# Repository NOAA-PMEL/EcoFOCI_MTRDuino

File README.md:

# EcoFOCI_MTRDuino

Arduino Version of PMEL's MTR (Miniature Temperature Recorder)

################

Legal Disclaimer

This repository is a software product and is not official communication of the National Oceanic and Atmospheric Administration (NOAA), or the United States Department of Commerce (DOC). All NOAA GitHub project code is provided on an 'as is' basis and the user assumes responsibility for its use. Any claims against the DOC or DOC bureaus stemming from the use of this GitHub project will be governed by all applicable Federal law. Any reference to specific commercial products, processes, or services by service mark, trademark, manufacturer, or otherwise, does not constitute or imply their endorsement, recommendation, or favoring by the DOC. The DOC seal and logo, or the seal and logo of a DOC bureau, shall not be used in any manner to imply endorsement of any commercial product or activity by the DOC or the United States Government.

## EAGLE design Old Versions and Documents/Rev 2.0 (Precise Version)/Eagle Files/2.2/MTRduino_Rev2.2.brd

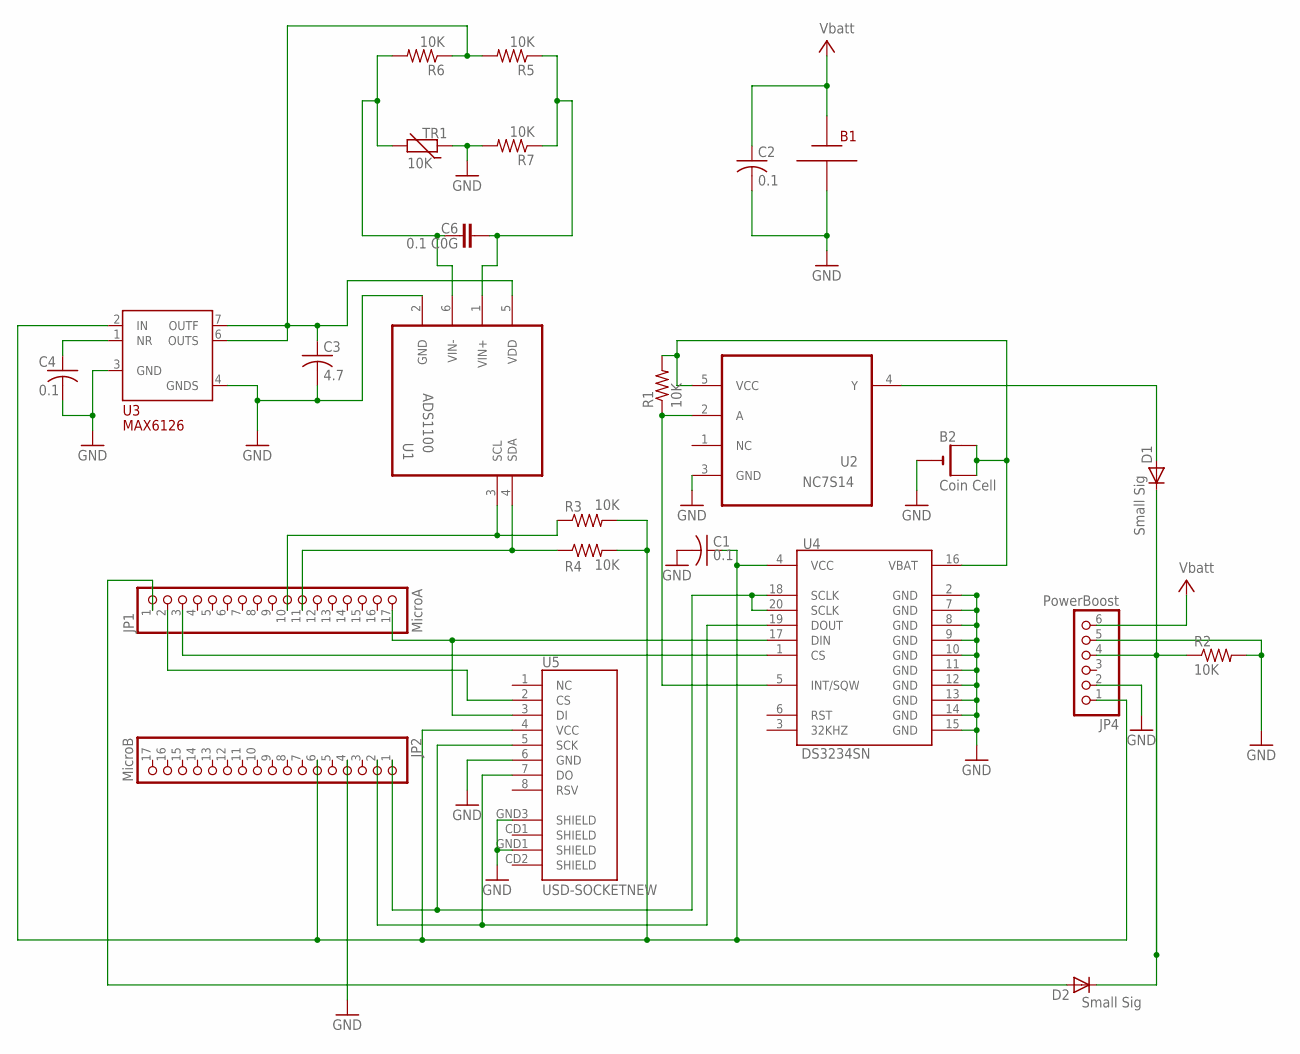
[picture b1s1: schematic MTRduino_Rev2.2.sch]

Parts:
B1: 2x AA BATT; BATT_AA2
B2: Coin Cell; CR1220-SMD
C1, C2, C4: 0.1; C0603
C3: 4.7; C0603
C6: 0.1 C0G; C0603
D1, D2: Small Sig; SOD-323F
JP1: MicroA; 1X17
JP2: MicroB; 1X17
JP4: PowerBoost; 1X06
R1, R2, R3, R4, R5, R6, R7: 10K; R0603
TR1: 10K; R-5
U1: ADS1100; SOT95P280X145-6N
U2: NC7S14; SOT95P280X145-5N
U3: MAX6126; SOIC127P600X175-8N
U4: DS3234SN; DS3234
U5: USD-SOCKETNEW; MICRO-SD-SOCKET-PP

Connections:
GND: B1.-, B2.-, C1.2, C2.2, C3.2, C4.2, JP2.4, JP4.2, JP4.5, R2.2, R7.2, TR1.1, U1.2 (GND), U2.3 (GND), U3.3 (GND), U3.4 (GNDS), U4.2 (GND), U4.7 (GND), U4.8 (GND), U4.9 (GND), U4.10 (GND), U4.11 (GND), U4.12 (GND), U4.13 (GND), U4.14 (GND), U4.15 (GND), U5.6 (GND), U5.GND1 (SHIELD), U5.GND3 (SHIELD)
unnamed: D1.A, U2.4 (Y)
unnamed: C6.1, R6.2, TR1.2, U1.6 (VIN-)
unnamed: JP1.3, U4.1 (CS)
unnamed: C4.1, U3.1 (NR)
unnamed: C6.2, R5.1, R7.1, U1.1 (VIN+)
unnamed: B2.+$1 (+), B2.+$2 (+1), R1.2, U2.5 (VCC), U4.16 (VBAT)
unnamed: JP1.17, U4.17 (DIN), U5.3 (DI)
unnamed: JP1.10, R3.1, U1.3 (SCL)
unnamed: JP1.11, R4.1, U1.4 (SDA)
unnamed: C3.1, R5.2, R6.1, U1.5 (VDD), U3.6 (OUTS), U3.7 (OUTF)
unnamed: R1.1, U2.2 (A), U4.5 (INT/SQW)
unnamed: JP2.2, U4.19 (DOUT), U5.7 (DO)
unnamed: D2.A, JP1.1
unnamed: D1.C, D2.C, JP4.4, R2.1
unnamed: JP2.1, U4.18 (SCLK), U4.20 (SCLK), U5.5 (SCK)
unnamed: C1.1, JP2.6, JP4.1, R3.2, R4.2, U3.2 (IN), U4.4 (VCC), U5.4 (VCC)
unnamed: JP1.2, U5.2 (CS)
V+: B1.+, C2.1, JP4.6

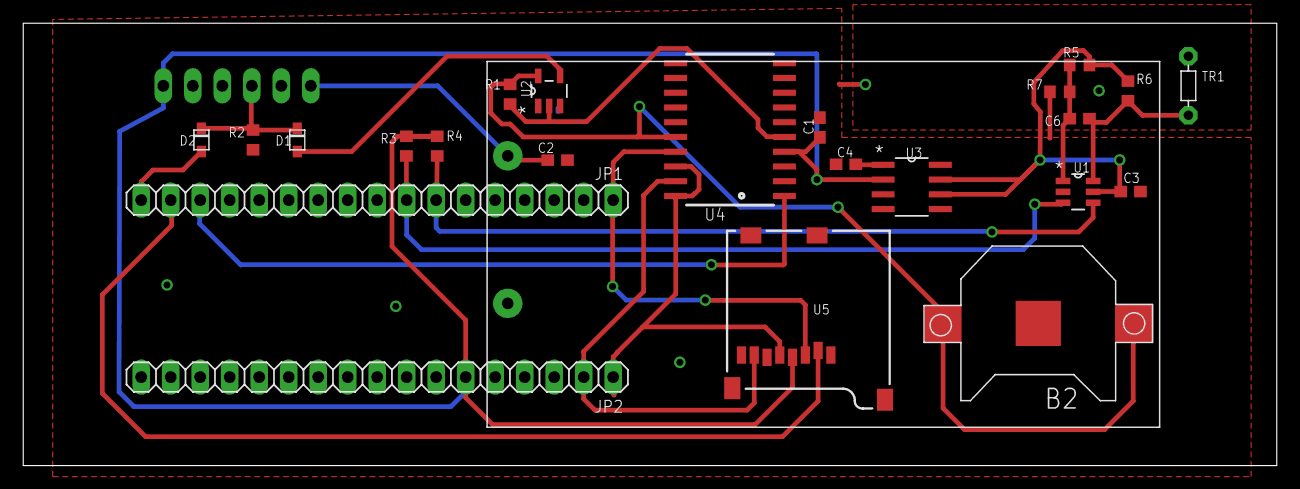
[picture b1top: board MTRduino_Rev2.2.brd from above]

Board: 2 copper layers, 107.9 x 38.1 mm, 25 parts (1 on the bottom side), 19 nets.

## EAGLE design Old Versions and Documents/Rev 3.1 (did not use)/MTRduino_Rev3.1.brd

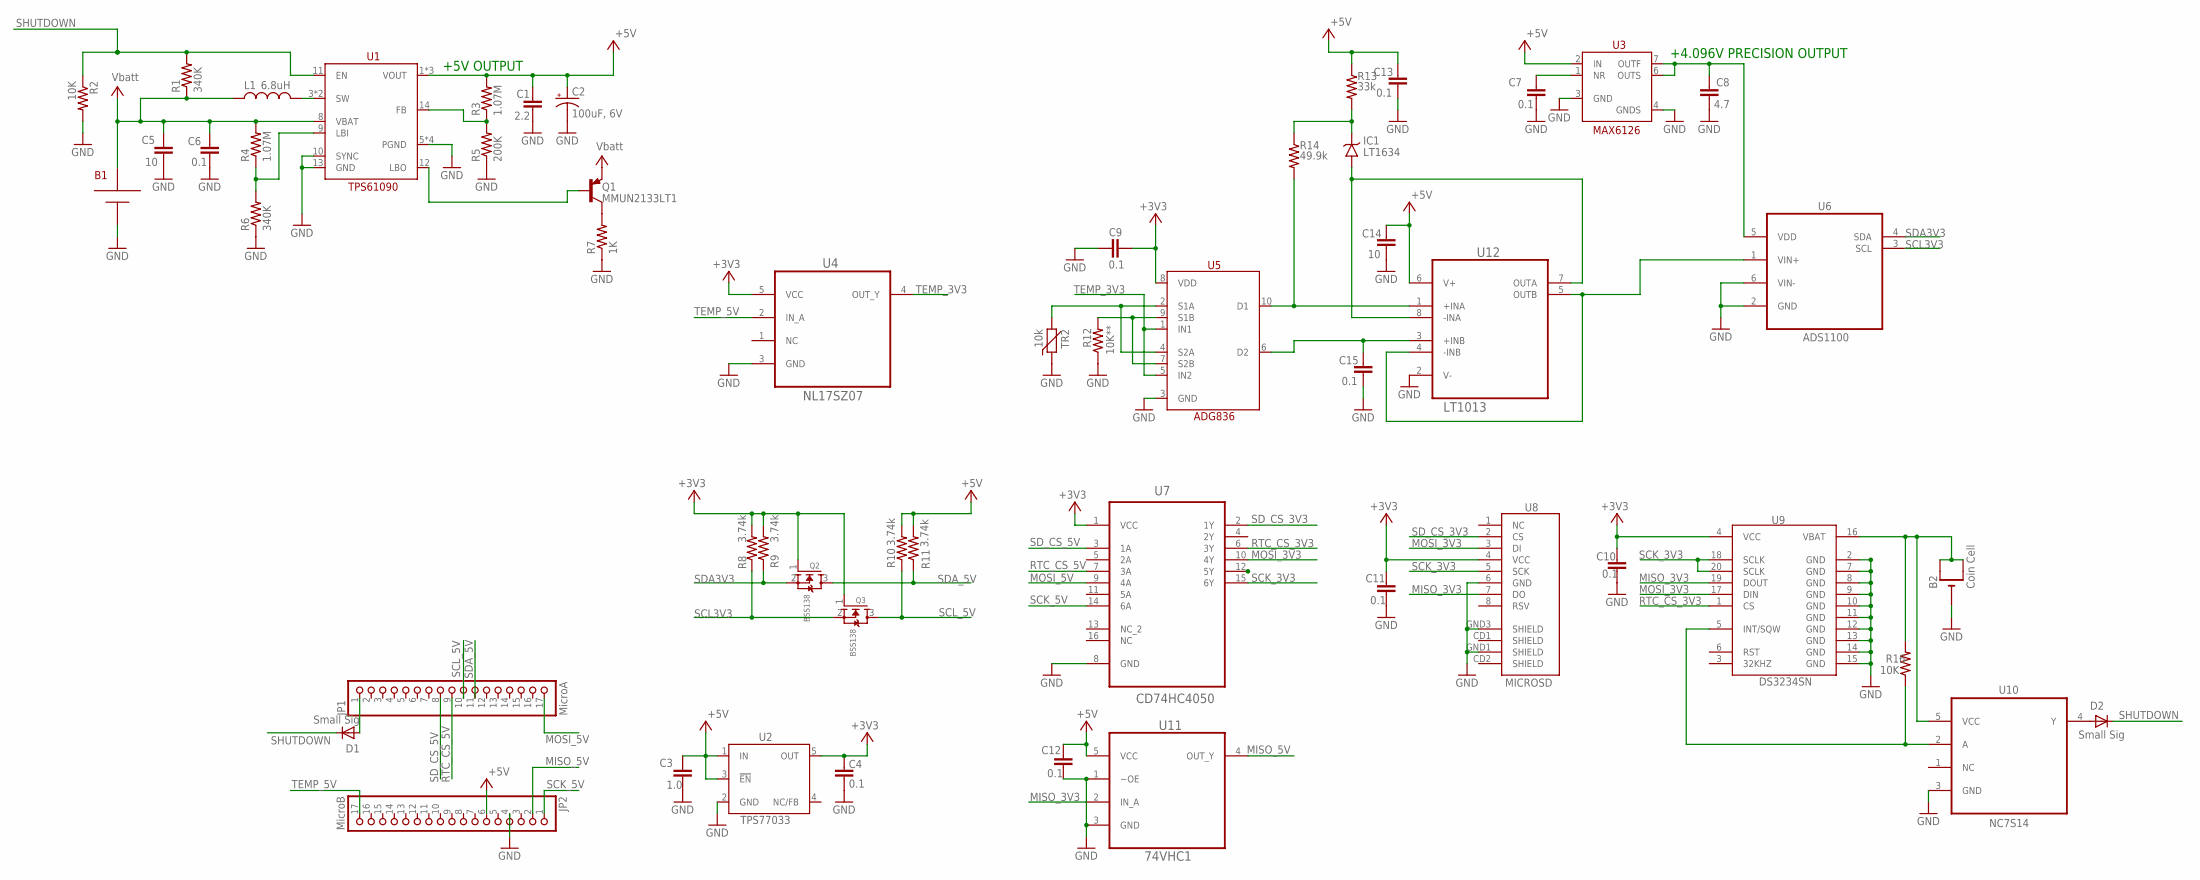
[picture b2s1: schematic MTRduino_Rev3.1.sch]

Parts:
B1: 2x AA BATT; BATT_AA2
B2: Coin Cell; CR1220-SMD
C1: 2.2; C0603
C2: 100uF, 6V; A/3216-18R
C3: 1.0; C0603
C4, C6, C7, C9, C10, C11, C12, C13, C15: 0.1; C0603
C5, C14: 10; C0603
C8: 4.7; C0603
D1, D2: Small Sig; SOD-323F
IC1: LT1634; S8
JP1: MicroA; 1X17
JP2: MicroB; 1X17
L1: 6.8uH; L2012C
Q1: MMUN2133LT1; SC59-BEC
Q2, Q3: BSS138; SOT23
R1, R6: 340K; R0603
R2, R16: 10K; R0603
R3, R4: 1.07M; R0603
R5: 200K; R0603
R7: 1K; R0603
R8, R9, R10, R11: 3.74k; R0603
R12: 10K**; R1206
R13: 33k; R0603
R14: 49.9k; R0603
TR2: 10k; R-5
U1: TPS61090; QFN16-4X4
U2: TPS77033; SOT23-DBV
U3: MAX6126; SOIC127P600X175-8N
U4: NL17SZ07; SOT65P210X110-5N
U5: ADG836; MSOP10
U6: ADS1100; SOT95P280X145-6N
U7: CD74HC4050; SOIC127P600X175-16N
U8: MICROSD; MICRO-SD-SOCKET-PP
U9: DS3234SN; DS3234
U10: NC7S14; SOT95P280X145-5N
U11: 74VHC1; SOT65P210X110-5N
U12: LT1013; SOIC127P600X175-8N

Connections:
+3V3: C4.1, C9.2, C10.1, C11.1, Q2.1 (G), Q3.1 (G), R8.2, R9.2, U2.5 (OUT), U4.5 (VCC), U5.8 (VDD), U7.1 (VCC), U8.4 (VCC), U9.4 (VCC)
+5V: C1.1, C2.+, C3.1, C12.1, C13.2, C14.2, JP2.6, R3.2, R10.2, R11.2, R13.1, U1.1 (VOUT), U1.15 (VOUT), U1.16 (VOUT), U2.1 (IN), U2.3 (!EN), U3.2 (IN), U11.5 (VCC), U12.6 (V+)
GND: B1.+, B2.-, C1.2, C2.-, C3.2, C4.2, C5.2, C6.2, C7.2, C8.2, C9.1, C10.2, C11.2, C12.2, C13.1, C14.1, C15.1, JP2.4, R2.2, R5.1, R6.1, R7.1, R12.1, TR2.1, U1.5 (PGND), U1.6 (PGND), U1.7 (PGND), U1.10 (SYNC), U1.13 (GND), U1.EXP (PGND), U2.2 (GND), U3.3 (GND), U3.4 (GNDS), U4.3 (GND), U5.3 (GND), U6.2 (GND), U6.6 (VIN-), U7.8 (GND), U8.6 (GND), U8.GND1 (SHIELD), U8.GND3 (SHIELD), U9.2 (GND), U9.7 (GND), U9.8 (GND), U9.9 (GND), U9.10 (GND), U9.11 (GND), U9.12 (GND), U9.13 (GND), U9.14 (GND), U9.15 (GND), U10.3 (GND), U11.1 (~OE), U11.3 (GND), U12.2 (V-)
MISO_3V3: U8.7 (DO), U9.19 (DOUT), U11.2 (IN_A)
MISO_5V: JP2.2, U11.4 (OUT_Y)
MOSI_3V3: U7.10 (4Y), U8.3 (DI), U9.17 (DIN)
MOSI_5V: JP1.17, U7.9 (4A)
unnamed: D2.A, U10.4 (Y)
unnamed: C15.2, U5.6 (D2), U12.3 (+INB)
unnamed: C7.1, U3.1 (NR)
unnamed: U6.1 (VIN+), U12.4 (-INB), U12.5 (OUTB)
unnamed: B2.+$1 (+), B2.+$2 (+1), R16.2, U9.16 (VBAT), U10.5 (VCC)
unnamed: L1.2, U1.3 (SW), U1.4 (SW)
unnamed: IC1.6 (VOUT), R13.2, R14.1
unnamed: TR2.2, U5.2 (S1A), U5.4 (S2A)
unnamed: R12.2, U5.7 (S2B), U5.9 (S1B)
unnamed: R4.1, R6.2, U1.9 (LBI)
unnamed: Q1.C, R7.2
unnamed: R3.1, R5.2, U1.14 (FB)
unnamed: IC1.4 (GND), U12.7 (OUTA), U12.8 (-INA)
unnamed: R14.2, U5.10 (D1), U12.1 (+INA)
unnamed: R16.1, U9.5 (INT/SQW), U10.2 (A)
unnamed: Q1.B, U1.12 (LBO)
unnamed: D1.A, JP1.1
unnamed: C8.1, U3.6 (OUTS), U3.7 (OUTF), U6.5 (VDD)
RTC_CS_3V3: U7.6 (3Y), U9.1 (CS)
RTC_CS_5V: JP1.9, U7.7 (3A)
SCK_3V3: U7.15 (6Y), U8.5 (SCK), U9.18 (SCLK), U9.20 (SCLK)
SCK_5V: JP2.1, U7.14 (6A)
SCL3V3: Q3.2 (S), R8.1, U6.3 (SCL)
SCL_5V: JP1.10, Q3.3 (D), R10.1
SDA3V3: Q2.2 (S), R9.1, U6.4 (SDA)
SDA_5V: JP1.11, Q2.3 (D), R11.1
SD_CS_3V3: U7.2 (1Y), U8.2 (CS)
SD_CS_5V: JP1.8, U7.3 (1A)
SHUTDOWN: D1.C, D2.C, R1.2, R2.1, U1.11 (EN)
TEMP_3V3: U4.4 (OUT_Y), U5.1 (IN1), U5.5 (IN2)
TEMP_5V: JP2.17, U4.2 (IN_A)
V+: B1.-, C5.1, C6.1, L1.1, Q1.E, R1.1, R4.2, U1.8 (VBAT)

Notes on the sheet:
+5V OUTPUT
+4.096V PRECISION OUTPUT

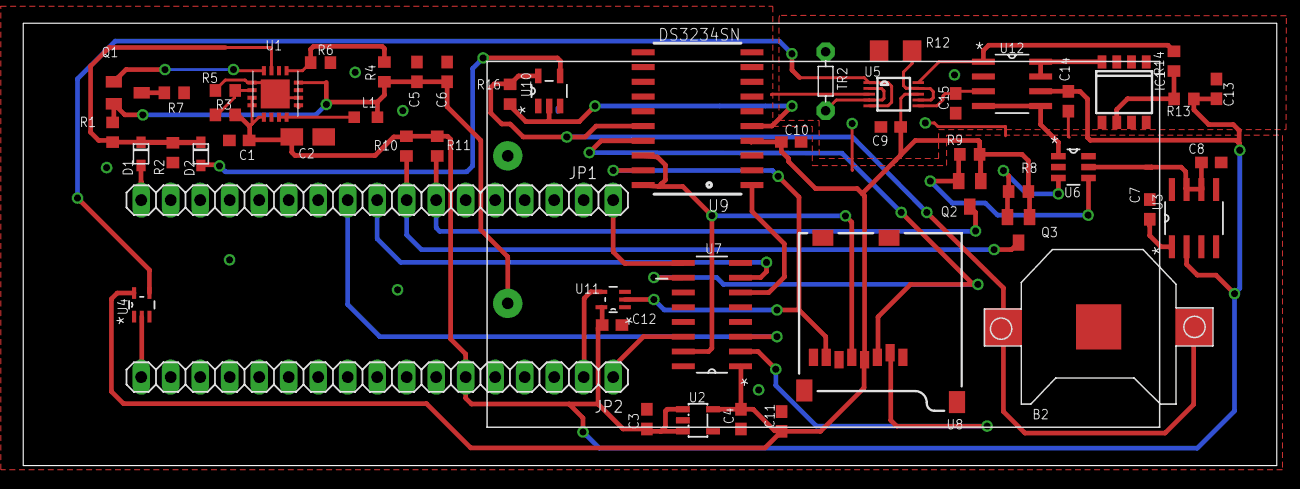
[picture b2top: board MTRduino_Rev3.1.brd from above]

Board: 2 copper layers, 107.9 x 38.1 mm, 54 parts (0 on the bottom side), 39 nets.

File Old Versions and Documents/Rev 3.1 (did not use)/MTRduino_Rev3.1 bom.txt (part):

Partlist exported from C:/Users/langis/Documents/eagle/MTRDuino/rev3.1/MTRduino_Rev3.1.sch at 4/27/2016 12:15:43 PM

Part Value         Device            Package             Description                                            MF                MPN              OC_FARNELL OC_NEWARK PACKAGE   SUPPLIER          
B1   2x AA BATT    BATT_AA2          BATT_AA2                                                                                                                                                       
B2   Coin Cell     CR1220SMT         CR1220-SMD          CR1216/CR1220/CR1225 12mm 3V lithium coin cell                                                                                             
C1   2.2           C-EUC0603         C0603               CAPACITOR, European symbol                                                                                                                 
C2   100uF, 6V     CPOL-USA/3216-18R A/3216-18R          POLARIZED CAPACITOR, American symbol                                                                                                       
C3   1.0           C-EUC0603         C0603               CAPACITOR, European symbol                                                                                                                 
C4   0.1           C-EUC0603         C0603               CAPACITOR, European symbol                                                                                                                 
C5   10            C-EUC0603         C0603               CAPACITOR, European symbol                                                                                                                 
C6   0.1           C-EUC0603         C0603               CAPACITOR, European symbol                                                                                                                 
C7   0.1           C-EUC0603         C0603               CAPACITOR, European symbol                                                                                                                 
C8   4.7           C-EUC0603         C0603               CAPACITOR, European symbol                                                                                                                 
C9   0.1           C-EUC0603         C0603               CAPACITOR, European symbol                                                                                                                 
C10  0.1           C-EUC0603         C0603               CAPACITOR, European symbol                                                                                                                 
C11  0.1           C-EUC0603         C0603               CAPACITOR, European symbol                                                                                                                 
C12  0.1           C-EUC0603         C0603               CAPACITOR, European symbol                                                                                                                 
D1   Small Sig     DIODESOD-323F     SOD-323F            Diode                                                                                                                                      
D2   Small Sig     DIODESOD-323F     SOD-323F            Diode                                                                                                                                      
JP1  MicroA        PINHD-1X17        1X17                PIN HEADER                                                                                                                                 
JP2  MicroB        PINHD-1X17        1X17                PIN HEADER                                                                                                                                 
L1   6.8uH         L-USL2012C        L2012C              INDUCTOR, American symbol                                                                                                                  
Q1   MMUN2133LT1   MMUN2111LT1       SC59-BEC            PNP Transistror                                                                                                                            
Q2   BSS138        MOSFET-NREFLOW    SOT23               N-Channel Mosfet                                                                                                                           
Q3   BSS138        MOSFET-NREFLOW    SOT23               N-Channel Mosfet                                                                                                                           
R1   340K          R-US_R0603        R0603               RESISTOR, American symbol                                                                                                                  
R2   10K           R-US_R0603        R0603               RESISTOR, American symbol                                                                                                                  
R3   1.07M         R-US_R0603        R0603               RESISTOR, American symbol                                                                                                                  
R4   1.07M         R-US_R0603        R0603               RESISTOR, American symbol                                                                                                                  
R5   200K          R-US_R0603        R0603               RESISTOR, American symbol                                                                                                                  
R6   340K          R-US_R0603        R0603               RESISTOR, American symbol                                                                                                                  
R7   1K            R-US_R0603        R0603               RESISTOR, American symbol                                                                                                                  
R8   3.75k         R-US_R0603        R0603               RESISTOR, American symbol                                                                                                                  
R9   3.75k         R-US_R0603        R0603               RESISTOR, American symbol                                                                                                                  
R10  3.75k         R-US_R0603        R0603               RESISTOR, American symbol                                                                                                                  
R11  3.75k         R-US_R0603        R0603               RESISTOR, American symbol                                                                                                                  
R12  10k,0.2ppm    R-US_R1206        R1206               RESISTOR, American symbol                                                                                                                  
R13  10K           R-US_R0603        R0603               RESISTOR, American symbol                                                                                                                  
R14  10K           R-US_R0603        R0603               RESISTOR, American symbol                                                                                                                  
R15  10K           R-US_R0603        R0603               RESISTOR, American symbol                                                                                                                  
R16  10K           R-US_R0603        R0603               RESISTOR, American symbol                                                                                                                  
TR1  10k           THERMISTOR_R-5    R-5                 Thermo Resistor                                                                                                                            
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
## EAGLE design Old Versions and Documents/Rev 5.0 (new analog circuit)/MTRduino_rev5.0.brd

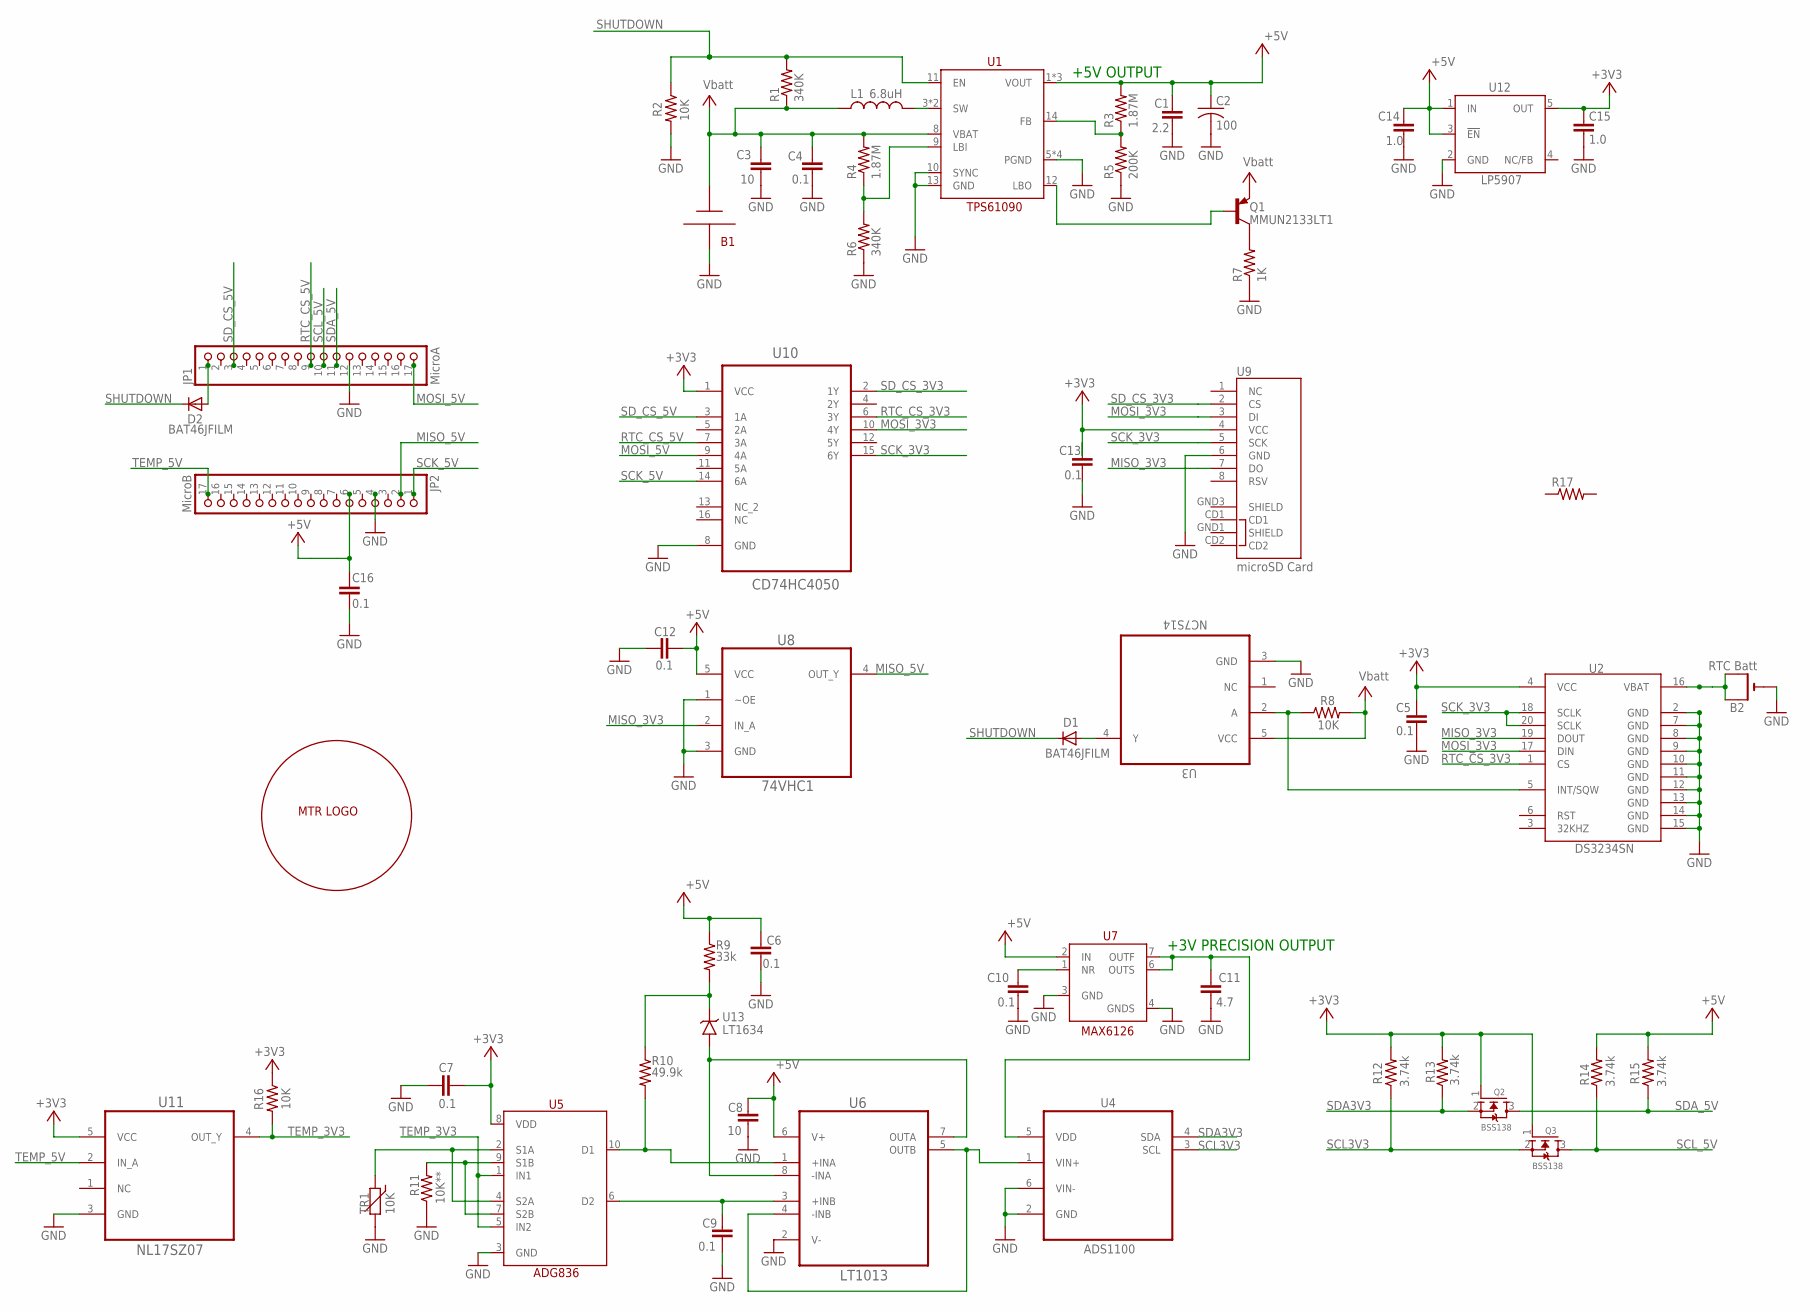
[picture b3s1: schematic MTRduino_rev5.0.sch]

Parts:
B1: 2x AA BATT; BATT_AA2
B2: RTC Batt; CR1220-SMD
C1: 2.2; C0603
C2: 100; C1206K
C3, C8: 10; C0603
C4, C5, C6, C7, C9, C10, C12, C13, C16: 0.1; C0603
C11: 4.7; C0603
C14, C15: 1.0; C0603
D1, D2: BAT46JFILM; SOD323-R
JP1: MicroA; 1X17
JP2: MicroB; 1X17
L1: 6.8uH; VLC6045
Q1: MMUN2133LT1; SC59-BEC
Q2, Q3: BSS138; SOT23
R1, R6: 340K; R0603
R2, R8, R16: 10K; R0603
R3, R4: 1.87M; R0805
R5: 200K; R0603
R7: 1K; R0603
R9: 33k; R0603
R10: 49.9k; R0603
R11: 10K**; R1206
R12, R13, R14, R15: 3.74k; R0603
R17: R-US_R0805; R0805
TR1: 10K; R-5
U1: TPS61090; QFN16-4X4
U2: DS3234SN; DS3234
U3: NC7S14; SOT95P280X145-5N
U4: ADS1100; SOT95P280X145-6N
U5: ADG836; MSOP10
U6: LT1013; SOIC127P600X175-8N
U7: MAX6126; SOIC127P600X175-8N
U8: 74VHC1; SOT65P210X110-5N
U9: microSD Card; MICROSD_1:1
U10: CD74HC4050; SOIC127P600X175-16N
U11: NL17SZ07; SOT65P210X110-5N
U12: LP5907; SOT23-DBV
U13: LT1634; S8
U$1: MTRLOGO

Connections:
+3V3: C5.1, C7.2, C13.1, C15.1, Q2.1 (G), Q3.1 (G), R12.2, R13.2, R16.1, U2.4 (VCC), U5.8 (VDD), U9.4 (VCC), U10.1 (VCC), U11.5 (VCC), U12.5 (OUT)
+5V: C1.1, C2.1, C6.2, C8.2, C12.1, C14.1, C16.1, JP2.6, R3.2, R9.1, R14.2, R15.2, U1.1 (VOUT), U1.15 (VOUT), U1.16 (VOUT), U6.6 (V+), U7.2 (IN), U8.5 (VCC), U12.1 (IN), U12.3 (!EN)
GND: B1.- (+), B2.-, C1.2, C2.2, C3.2, C4.2, C5.2, C6.1, C7.1, C8.1, C9.1, C10.2, C11.2, C12.2, C13.2, C14.2, C15.2, C16.2, JP1.12, JP2.4, R2.2, R5.1, R6.1, R7.1, R11.1, TR1.2, U1.5 (PGND), U1.6 (PGND), U1.7 (PGND), U1.10 (SYNC), U1.13 (GND), U1.EXP (PGND), U2.2 (GND), U2.7 (GND), U2.8 (GND), U2.9 (GND), U2.10 (GND), U2.11 (GND), U2.12 (GND), U2.13 (GND), U2.14 (GND), U2.15 (GND), U3.3 (GND), U4.2 (GND), U4.6 (VIN-), U5.3 (GND), U6.2 (V-), U7.3 (GND), U7.4 (GNDS), U8.1 (~OE), U8.3 (GND), U9.6 (GND), U10.8 (GND), U11.3 (GND), U12.2 (GND)
MISO_3V3: U2.19 (DOUT), U8.2 (IN_A), U9.7 (DO)
MISO_5V: JP2.2, U8.4 (OUT_Y)
MOSI_3V3: U2.17 (DIN), U9.3 (DI), U10.10 (4Y)
MOSI_5V: JP1.17, U10.9 (4A)
unnamed: D1.A, U3.4 (Y)
unnamed: C9.2, U5.6 (D2), U6.3 (+INB)
unnamed: C10.1, U7.1 (NR)
unnamed: U4.1 (VIN+), U6.4 (-INB), U6.5 (OUTB)
unnamed: B2.+$1 (+), B2.+$2 (+1), U2.16 (VBAT)
unnamed: L1.P$3 (2), U1.3 (SW), U1.4 (SW)
unnamed: R9.2, R10.1, U13.6 (VOUT)
unnamed: TR1.1, U5.2 (S1A), U5.4 (S2A)
unnamed: R11.2, U5.7 (S2B), U5.9 (S1B)
unnamed: R4.1, R6.2, U1.9 (LBI)
unnamed: Q1.C, R7.2
unnamed: R3.1, R5.2, U1.14 (FB)
unnamed: U6.7 (OUTA), U6.8 (-INA), U13.4 (GND)
unnamed: R10.2, U5.10 (D1), U6.1 (+INA)
unnamed: R8.1, U2.5 (INT/SQW), U3.2 (A)
unnamed: Q1.B, U1.12 (LBO)
unnamed: D2.A, JP1.1
unnamed: C11.1, U4.5 (VDD), U7.6 (OUTS), U7.7 (OUTF)
RTC_CS_3V3: U2.1 (CS), U10.6 (3Y)
RTC_CS_5V: JP1.9, U10.7 (3A)
SCK_3V3: U2.18 (SCLK), U2.20 (SCLK), U9.5 (SCK), U10.15 (6Y)
SCK_5V: JP2.1, U10.14 (6A)
SCL3V3: Q3.2 (S), R12.1, U4.3 (SCL)
SCL_5V: JP1.10, Q3.3 (D), R14.1
SDA3V3: Q2.2 (S), R13.1, U4.4 (SDA)
SDA_5V: JP1.11, Q2.3 (D), R15.1
SD_CS_3V3: U9.2 (CS), U10.2 (1Y)
SD_CS_5V: JP1.3, U10.3 (1A)
SHUTDOWN: D1.C, D2.C, R1.2, R2.1, U1.11 (EN)
TEMP_3V3: R16.2, U5.1 (IN1), U5.5 (IN2), U11.4 (OUT_Y)
TEMP_5V: JP2.17, U11.2 (IN_A)
V+: B1.+ (-), C3.1, C4.1, L1.P$2 (1), Q1.E, R1.1, R4.2, R8.2, U1.8 (VBAT), U3.5 (VCC)

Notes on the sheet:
+5V OUTPUT
+3V PRECISION OUTPUT

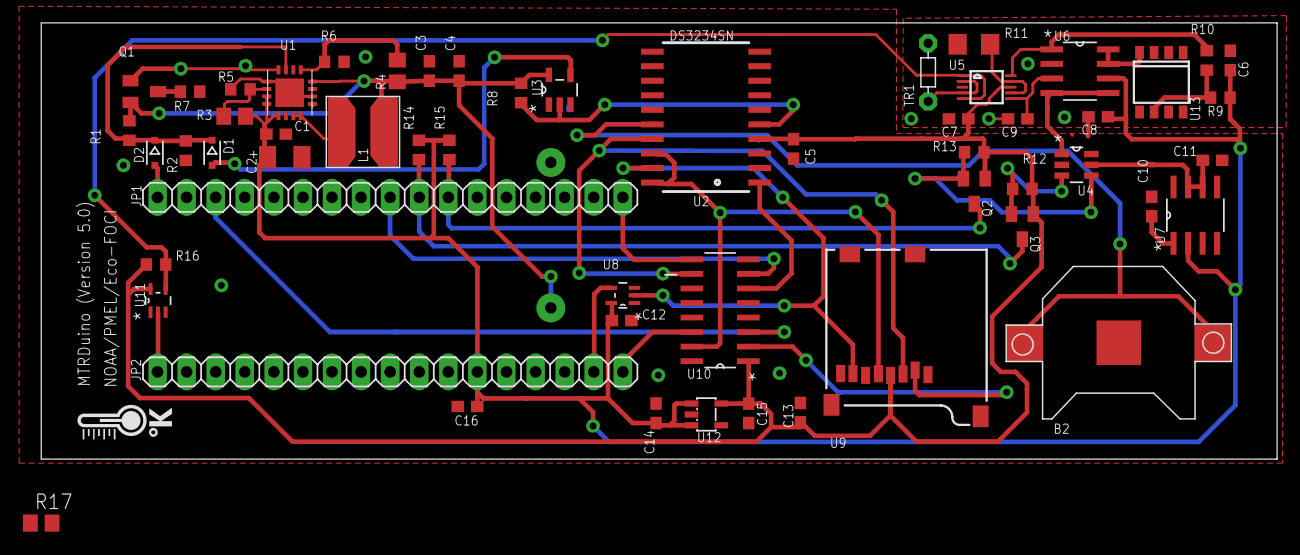
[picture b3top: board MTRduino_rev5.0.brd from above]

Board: 2 copper layers, 108.0 x 38.1 mm, 58 parts (1 on the bottom side), 39 nets.

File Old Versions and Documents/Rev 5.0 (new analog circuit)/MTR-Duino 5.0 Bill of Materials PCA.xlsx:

Identifier | Type | Description | Part Number | Qty | Notes
A1 | Arduino | ARDUINO MICRO | 1050-1066-ND | 1 | DO NOT POPULATE
B1 | Battery | HOLDER BATTERY 2CELL AA PC MNT | 36-2462-ND | 1 | DO NOT POPULATE
B2 | Battery | HOLDER BATTERY COIN 12MM DIA SMD | 36-3000CT-ND | 1 | Please place blob of solder on center pad
B3 | Battery | AA LITHIUM BATTERY | ENERGIZER L91 | 2 | DO NOT POPULATE
B4 | Battery | BATTERY LITHIUM 3V COIN 12.5MM | N033-ND | 1 | DO NOT POPULATE
C1 | Capacitor | CAP CER 2.2UF 10V X5R 0603 | 311-1451-1-ND | 1
C2 | Capacitor | CAP TANT 100UF 6.3V 10% 1206 | 478-8152-1-ND | 1
C3,C8 | Capacitor | CAP CER 10UF 6.3V X5R 0603 | 311-1781-1-ND | 2
C4,C5,C6,C7, C9,C10,C12,C13,C16 | Capacitor | CAP CER 0.1UF 50V X7R 0603 | 399-5089-1-ND | 9
C11 | Capacitor | CAP CER 4.7UF 10V X5R 0603 | 311-1455-1-ND | 1
C14,C15 | Capacitor | CAP CER 1UF 16V Y5V 0603 | 311-1372-1-ND | 2
D1,D2 | Diode | DIODE SCHOTTKY 100V 150MA SOD323 | 497-6653-1-ND | 2
JP1,JP2 | Header | SOCKET 7 MM SOLDER TAIL SINGLE | 1212-1195-ND | 2
JP1,JP2 | Header | SOCKET 7 MM SOLDER TAIL SINGLE | 1212-1188-ND | 2
L1 | Inductor | FIXED IND 6.8UH 3A 41 MOHM SMD | 810-VLC6045T-6R8M | 1
Q1 | Transistor | TRANS PREBIAS PNP 246MW SOT23-3 | MMUN2133LT1GOSCT-ND | 1
Q2,Q3 | Transistor | MOSFET N-CH 50V 220MA SOT-23 | BSS138CT-ND | 2
R1,R6 | Resistor | RES SMD 340K OHM 1% 1/10W 0603 | 311-340KHRCT-ND | 2
R2,R8,R16 | Resistor | RES SMD 10K OHM 1% 1/10W 0603 | 311-10.0KHRCT-ND | 3
R3,R4 | Resistor | RES SMD 1.87M OHM 1% 1/8W 0805 | P1.87BTCT-ND | 2
R5 | Resistor | RES SMD 200K OHM 1% 1/10W 0603 | 311-200KHRCT-ND | 1
R7 | Resistor | RES SMD 1K OHM 1% 1/10W 0603 | 311-1.00KHRCT-ND | 1
R9 | Resistor | RES SMD 33K OHM 1% 1/10W 0603 | 311-33.0KHRCT-ND | 1
R10 | Resistor | RES SMD 49.9K OHM 1% 1/10W 0603 | 311-49.9KHRCT-ND | 1
R11 | Resistor | RES SMD 10K OHM 0.01% 1/4W 1206 | Y1630-10.0KBCT-ND | 1
R12,R13,R14,R15 | Resistor | RES SMD 3.74K OHM 1% 1/10W 0603 | 311-3.74KHRCT-ND | 4
TR1 | Thermistor | NTC THERMISTOR 10K OHM 0.1C BEAD | 615-1003-ND | 1 | DO NOT POPULATE
U1 | IC | IC REG BOOST ADJ 2A SYNC 16VQFN | 296-15259-1-ND | 1
U2 | IC | IC RTC CLK/CALENDAR SPI 20-SOIC | DS3234SN#T&RCT-ND | 1
U3 | IC | IC INVERTER SCHMITT INPUT SOT-23 | NC7S14M5XCT-ND | 1
U4 | IC | IC ADC 16-BIT I2C PROGBL SOT23-6 | 296-14298-1-ND | 1
U5 | IC | IC SWITCH DUAL SPDT 10MSOP | ADG836LYRMZ-ND | 1
U6 | IC | IC OPAMP GP 1MHZ 8SOIC | 296-12982-1-ND | 1
U7 | IC | IC VREF SERIES 3V 8SOIC | MAX6126AASA30+-ND | 1
U8 | IC | IC BUFF CMOS LVL/SFTR N-I SOT353 | M74VHC1GT125DF1GOSCT-ND | 1
U9 | IC | CONN MICRO SD CARD PUSH-PUSH R/A | WM3288CT-ND | 1
U10 | IC | IC BUFF NON-INVERT 6V 16SOIC | 296-14529-1-ND | 1
U11 | IC | IC BUFF OP/DRAIN N-INV SOT353 | NL17SZ07DFT2GOSCT-ND | 1
U12 | IC | IC REG LDO 3.3V 0.25A SOT23-5 | 296-38557-1-ND | 1
U13 | IC | IC VREF SHUNT 1.25V 8SOIC | LT1634BIS8-1.25#PBF-ND | 1

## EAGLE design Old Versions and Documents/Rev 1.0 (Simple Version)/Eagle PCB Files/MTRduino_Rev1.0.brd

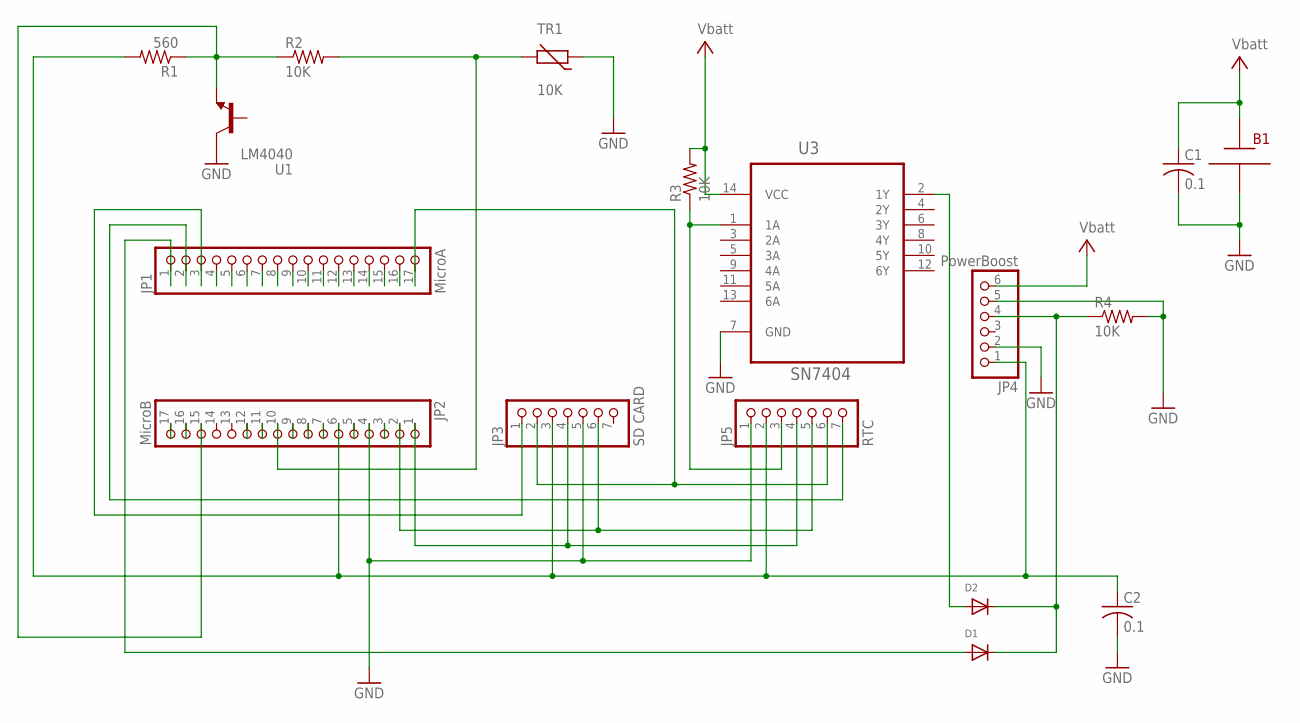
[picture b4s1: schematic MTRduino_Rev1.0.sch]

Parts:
B1: AA Batt; BATT_AA2
C1, C2: 0.1; C025-030X050
D1, D2: DIODEDO-1N4148; DO-1N4148
JP1: MicroA; 1X17
JP2: MicroB; 1X17
JP3: SD CARD; 1X07
JP4: PowerBoost; 1X06
JP5: RTC; 1X07
R1: 560; 0207/12
R2, R3, R4: 10K; 0207/12
TR1: 10K; R-5
U1: LM4040; TO92-BEC
U3: SN7404; DIP254P762X508-14

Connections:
GND: B1.-, C1.2, C2.2, JP2.4, JP3.5, JP4.2, JP4.5, JP5.1, R4.2, TR1.1, U1.C, U3.7 (GND)
unnamed: D2.A, U3.2 (1Y)
unnamed: JP1.2, JP5.7
unnamed: JP5.3, R3.1, U3.1 (1A)
unnamed: JP1.17, JP3.2, JP5.6
unnamed: D1.A, JP1.1
unnamed: JP2.10, R2.2, TR1.2
unnamed: D1.C, D2.C, JP4.4, R4.1
unnamed: JP2.15, R1.1, R2.1, U1.E
unnamed: JP2.1, JP3.4, JP5.4
unnamed: JP2.2, JP3.6, JP5.5
unnamed: C2.1, JP2.6, JP3.3, JP4.1, JP5.2, R1.2
unnamed: JP1.3, JP3.1
V+: B1.+, C1.1, JP4.6, R3.2, U3.14 (VCC)

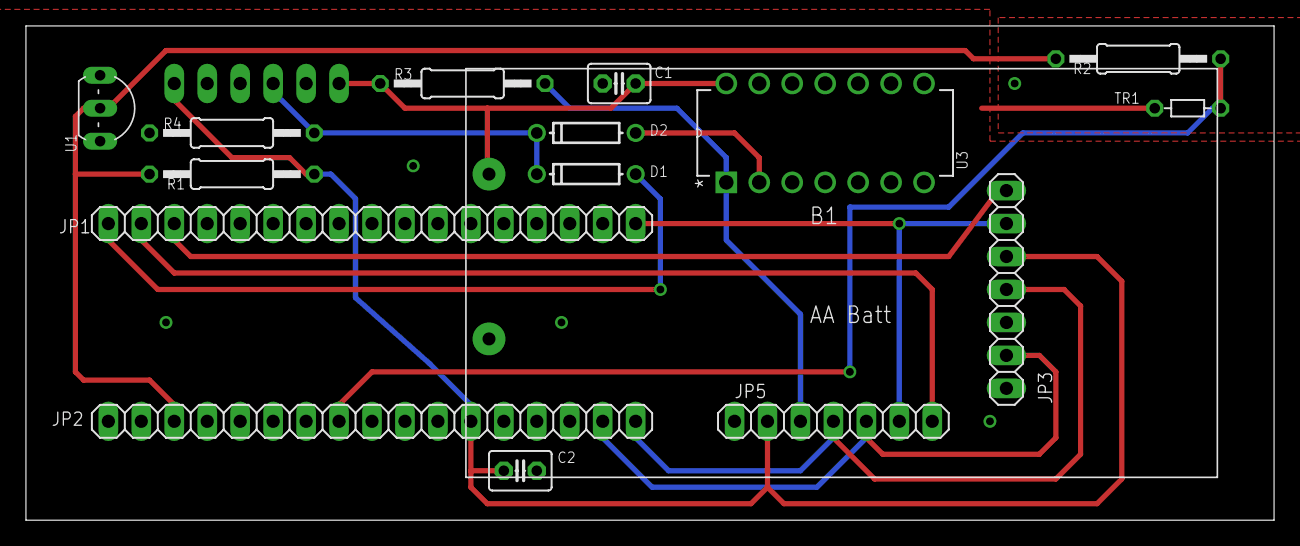
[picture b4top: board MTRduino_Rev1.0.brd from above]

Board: 2 copper layers, 96.2 x 38.1 mm, 17 parts (1 on the bottom side), 14 nets.

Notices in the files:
parts and their libraries:
SparkFun-FreqCtrl: Licensing: Creative Commons ShareAlike 4.0 International - https://creativecommons.org/licenses/by-sa/4.0
